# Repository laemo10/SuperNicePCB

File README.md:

# UWB Anchor & Indoor Human Occupancy Tracking Station

An integrated, multi-sensor UWB anchor PCB designed for real-time indoor object tracking (via Double-Sided Two-Way Ranging) and non-invasive human presence/occupancy monitoring. Built on a compact **75 × 85 mm²** 4-layer stackup, this node timestamps sensor data with microsecond precision via Wi-Fi TSF and streams payload telemetry to a central data fusion server.

## Table of Contents

* [Project Overview](#project-overview)
* [Key Features](#key-features)
* [Hardware & Bill of Materials](#hardware--bill-of-materials)
* [Sensor Matrix](#sensor-matrix)
* [Time Synchronization Strategy](#time-synchronization-strategy)
* [PCB Design & Stackup](#pcb-design--stackup)
* [Repository Structure](#repository-structure)
* [Team & Course Credits](#team--course-credits)

## Project Overview

This project implements an open-hardware anchor node for spatial localization and environmental occupancy analytics. The node performs two core functions simultaneously:

1. **Ultra-Wideband (UWB) Ranging:** Acts as a fixed anchor measuring distances to mobile UWB tags using IEEE 802.15.4z DS-TWR.
2. **Multi-Variable Human Sensing:** Tracks room occupancy trends and movement through non-camera environmental sensors (CO₂, Temperature/Humidity, Acoustic level, PIR motion, and mmWave micro-movement radar).

All gathered metrics are bound to a unified global timebase and transmitted over a 2.4 GHz Wi-Fi network (UDP/TCP) to a host server executing sensor-fusion algorithms.

## Key Features

* **High-Performance MCU:** ESP32-S3-WROOM-1-N8 (Dual-core Xtensa LX7 @ 240 MHz, 512 kB SRAM, 8 MB Flash, native USB CDC/JTAG).
* **Precision UWB Transceiver:** Decawave DWM3000TR13 (DW3110 engine) over SPI, supporting channels 5 (6.5 GHz) and 9 (8.0 GHz) with integrated antenna and keep-out area.
* **Dual 3.3V Power Domain Architecture:** Dedicated high-efficiency DC-DC Buck converter power rail for MCU processing and wireless transmission current spikes, combined with an isolated low-noise LDO regulator power rail for the sensitive sensor matrix.
* **Privacy-Preserving Human Detection:** Multi-variable sensing without optical cameras.
* **Microsecond Timestamping:** Hardware Wi-Fi TSF timer (`esp_wifi_get_tsf_time()`) combined with periodic NTP/SNTP synchronization.

## Hardware & Bill of Materials

| Function | Component MPN | Description | Interface | JLC Code |
| :--- | :--- | :--- | :--- | :--- |
| **MCU** | `ESP32-S3-WROOM-1-N8` | Dual-core Wi-Fi/BLE SoC (8 MB Flash) | SPI, I²C, UART, I²S | C2913198 |
| **UWB Transceiver** | `DWM3000TR13` | Integrated UWB Transceiver Module | SPI (20 MHz) | C5299931 |
| **MCU Power Rail** | `DC-DC Buck Regulator` | High-efficiency 3.3V Step-Down Converter (MCU) | Power | TBD |
| **Sensor Power Rail** | `Low-Noise LDO` | Dedicated Ultra-Low Noise 3.3V Regulator (Sensors) | Power | TBD |
| **Power Connector** | `HYCW263-USBC04-850B` | 16-Pin USB Type-C Receptacle | 5V Input | C3034197 |
| **CO₂ Sensor** | `Sensirion SCD40` | Photoacoustic NDIR CO₂ (0 - 40,000 ppm) | I²C | C3037696 |
| **Temp/RH** | `Sensirion SHT40-AD1B-R3` | Relative Humidity & Temperature Sensor | I²C | C2848306 |
| **Acoustic Sensor** | `TDK InvenSense ICS-43434` | Digital Omnidirectional MEMS Microphone | I²S | C5656610 |
| **PIR Motion** | `AM312` | Passive Infrared Human Motion Detector | GPIO | C114881 |
| **mmWave Radar** | `24/60 GHz mmWave Radar` | Micro-movement & Breathing Radar | UART | C37897213 |

## Sensor Matrix

1. **Decawave DWM3000 UWB:** Configured for Double-Sided Two-Way Ranging (DS-TWR) operating at 5 - 20 Hz update rates per tag.
2. **Sensirion SCD40:** Measures ambient CO₂ concentration every 30 - 60 s as an indicator of human breathing density.
3. **Sensirion SHT40:** Provides high-accuracy ambient thermal/humidity telemetry (±0.2 °C, ±1.8% RH) to complement indoor air comfort models.
4. **TDK ICS-43434:** Samples acoustic sound pressure over sliding time windows to determine room activity levels.
5. **AM312 PIR:** Digital motion trigger generating interrupts upon macroscopic body movement.
6. **mmWave Radar Module:** Captures fine target presence, velocity, and chest micro-movements (respiration) via continuous UART streaming.

## Time Synchronization Strategy

To ensure precise multi-anchor data alignment on the host processing server:

1. **Coarse Clock Sync (NTP/SNTP):** Upon Wi-Fi connection, the anchor queries an NTP server to calibrate epoch time.
2. **Fine-Grain Microsecond Timing (Wi-Fi TSF):** Each sensor frame is tagged using `esp_wifi_get_tsf_time()`, providing absolute microsecond precision relative to the Wi-Fi Access Point Timing Synchronization Function.
3. **Fallback Mode (ESP-NOW):** In ad-hoc deployments without an infrastructure AP, an ESP-NOW broadcast timesync protocol is utilized.

## PCB Design & Stackup

* **Dimensions:** 75 × 85 mm²
* **Layer Count:** 4 Layers (Mixed RF + High-Speed Digital)
* **Layer Assignment:**
  * **L1 (Top):** Component placement, high-speed signals (SPI, I²S, USB 90 Ω diff pair), RF traces.
  * **L2 (GND):** Continuous Solid Ground Plane.
  * **L3 (Power):** Split power planes with dual 3.3V power domains (3.3V_MCU from Buck, 3.3V_SENSOR from LDO).
  * **L4 (Bottom):** Secondary routing and test points.
* **RF Guidelines:** 50 Ω coplanar waveguide routing for UWB antenna path with explicit ground keep-out regions under the chip antenna area.

## Repository Structure

```
├── docs/
│   ├── schematics/             # PDF Schematics
│   └── specifications/         # ECAM Project Brief & Specs
├── hardware/
│   ├── gerber/                 # Production fabrication files
│   ├── KiCad/                  # Project files (.kicad_pro, .kicad_sch, .kicad_pcb)
│   └── bom/                    # Bill of Materials (CSV/JLCPCB format)
├── firmware/
│   ├── main/                   # ESP-IDF / Arduino source code
│   └── components/             # Custom drivers for SCD40, DWM3000, ICS-43434
└── README.md
```

## Team & Course Credits

**Course:** Advanced PCB Design (Academic Year 2026–2027)  
**Institution:** ECAM Brussels Engineering School  

**Group Members:**
* Laurent Emond
* Vincenzo Acquaviva
* Lincoln Lassey
* Mathieu Mascot

*ECAM Engineering Department*

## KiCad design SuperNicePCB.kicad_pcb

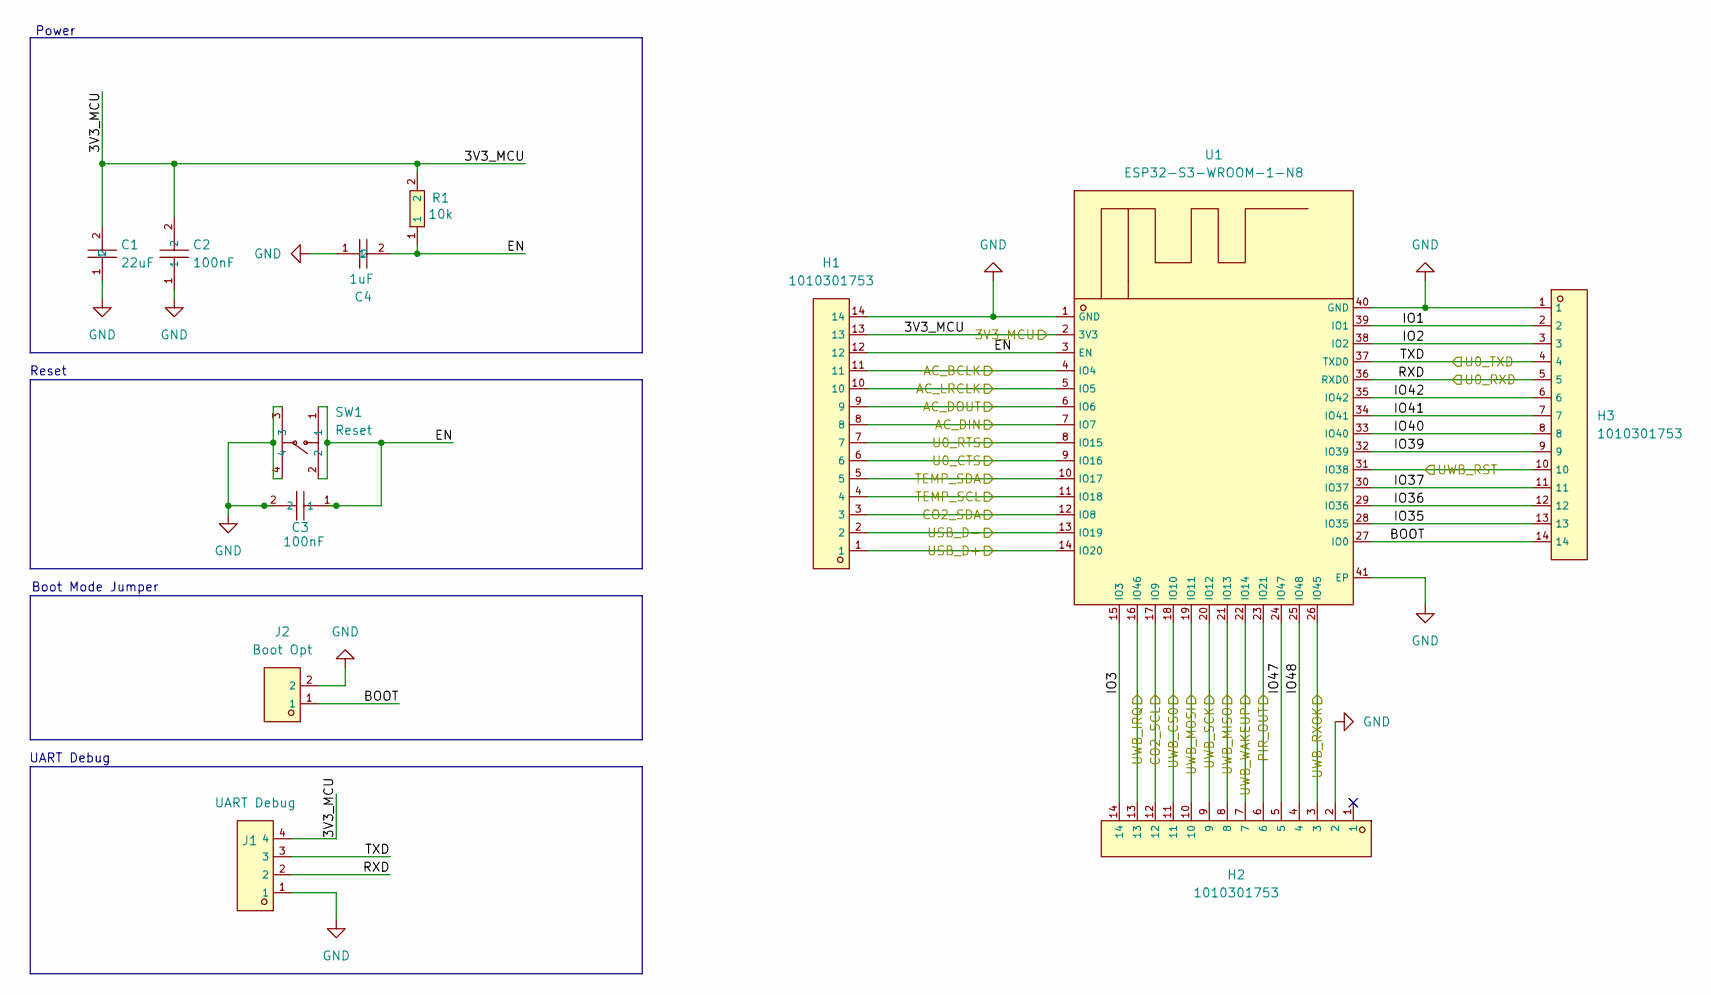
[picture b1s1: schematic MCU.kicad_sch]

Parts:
C1: 22uF; C1859_C1206; LCSC C1859
C2, C3: 100nF; C1525_C0402; LCSC C1525
C4: 1uF; C1592_C0603; LCSC C1592
H1, H2, H3: 1010301753; C52016809_HDR-SMD_14P-P2_54-V-M-S4_8; LCSC C52016809
J1: UART Debug; PinHeader_1x04_P1.27mm_Vertical_SMD_Pin1Left; LCSC C22438101
J2: Boot Opt; PinHeader_1x02_P1.27mm_Vertical_SMD_Pin1Left; LCSC C703015
R1: 10k; C1489_R1206; LCSC C1489
SW1: Reset; C55200589_SW-SMD_4P-L4_2-W3_4-P2_15-LS5_2; LCSC C55200589
U1: ESP32-S3-WROOM-1-N8; C2913198_WIFIM-SMD_ESP32-S3-WROOM-1-N8; LCSC C2913198

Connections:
/HumanSesors/AC_BCLK: H1.11, U1.4 (IO4); also elsewhere on the board
/HumanSesors/AC_LRCLK: H1.10, U1.5 (IO5); also elsewhere on the board
/HumanSesors/C02_SDA: H1.3, U1.12 (IO8); also elsewhere on the board
/HumanSesors/CO2_SCL: H2.12, U1.17 (IO9); also elsewhere on the board
/HumanSesors/DIN: H1.8, U1.7 (IO7); also elsewhere on the board
/HumanSesors/U0_CTS: H1.6, U1.9 (IO16); also elsewhere on the board
/HumanSesors/U0_RTS: H1.7, U1.8 (IO15); also elsewhere on the board
/MCU/3V3_MCU: C1.2, C2.2, H1.13, J1.4, R1.2, U1.2 (3V3); also elsewhere on the board
/MCU/AC_DOUT: H1.9, U1.6 (IO6)
/MCU/BOOT: H3.14, J2.1, U1.27 (IO0); also elsewhere on the board
/MCU/EN: C3.1, C4.2, H1.12, R1.1, SW1.1, SW1.2, U1.3 (EN)
/MCU/IO1: H3.2, U1.39 (IO1)
/MCU/IO2: H3.3, U1.38 (IO2)
/MCU/IO3: H2.14, U1.15 (IO3)
/MCU/IO35: H3.13, U1.28 (IO35)
/MCU/IO36: H3.12, U1.29 (IO36)
/MCU/IO37: H3.11, U1.30 (IO37)
/MCU/IO39: H3.9, U1.32 (IO39)
/MCU/IO40: H3.8, U1.33 (IO40)
/MCU/IO41: H3.7, U1.34 (IO41)
/MCU/IO42: H3.6, U1.35 (IO42)
/MCU/IO47: H2.5, U1.24 (IO47)
/MCU/IO48: H2.4, U1.25 (IO48)
/MCU/RXD: H3.5, J1.2, U1.36 (RXD0); also elsewhere on the board
/MCU/TXD: H3.4, J1.3, U1.37 (TXD0); also elsewhere on the board
/MCU/UWB_CS0: H2.11, U1.18 (IO10); also elsewhere on the board
/MCU/UWB_IRQ: H2.13, U1.16 (IO46); also elsewhere on the board
/MCU/UWB_MISO: H2.8, U1.21 (IO13); also elsewhere on the board
/MCU/UWB_MOSI: H2.10, U1.19 (IO11); also elsewhere on the board
/MCU/UWB_RST: H3.10, U1.31 (IO38); also elsewhere on the board
/MCU/UWB_RXOK: H2.3, U1.26 (IO45); also elsewhere on the board
/MCU/UWB_SCK: H2.9, U1.20 (IO12); also elsewhere on the board
/MCU/UWB_WAKEUP: H2.7, U1.22 (IO14); also elsewhere on the board
/PIR_OUT: H2.6, U1.23 (IO21); also elsewhere on the board
/TEMP_SCL: H1.4, U1.11 (IO18); also elsewhere on the board
/TEMP_SDA: H1.5, U1.10 (IO17); also elsewhere on the board
/USB_D+: H1.1, U1.14 (IO20); also elsewhere on the board
/USB_D-: H1.2, U1.13 (IO19); also elsewhere on the board
GND: C1.1, C2.1, C3.2, C4.1, H1.14, H2.2, H3.1, J1.1, J2.2, SW1.3, SW1.4, U1.1 (GND), U1.40 (GND), U1.41 (EP); also elsewhere on the board

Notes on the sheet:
Boot Mode Jumper
Power
UART Debug
Reset

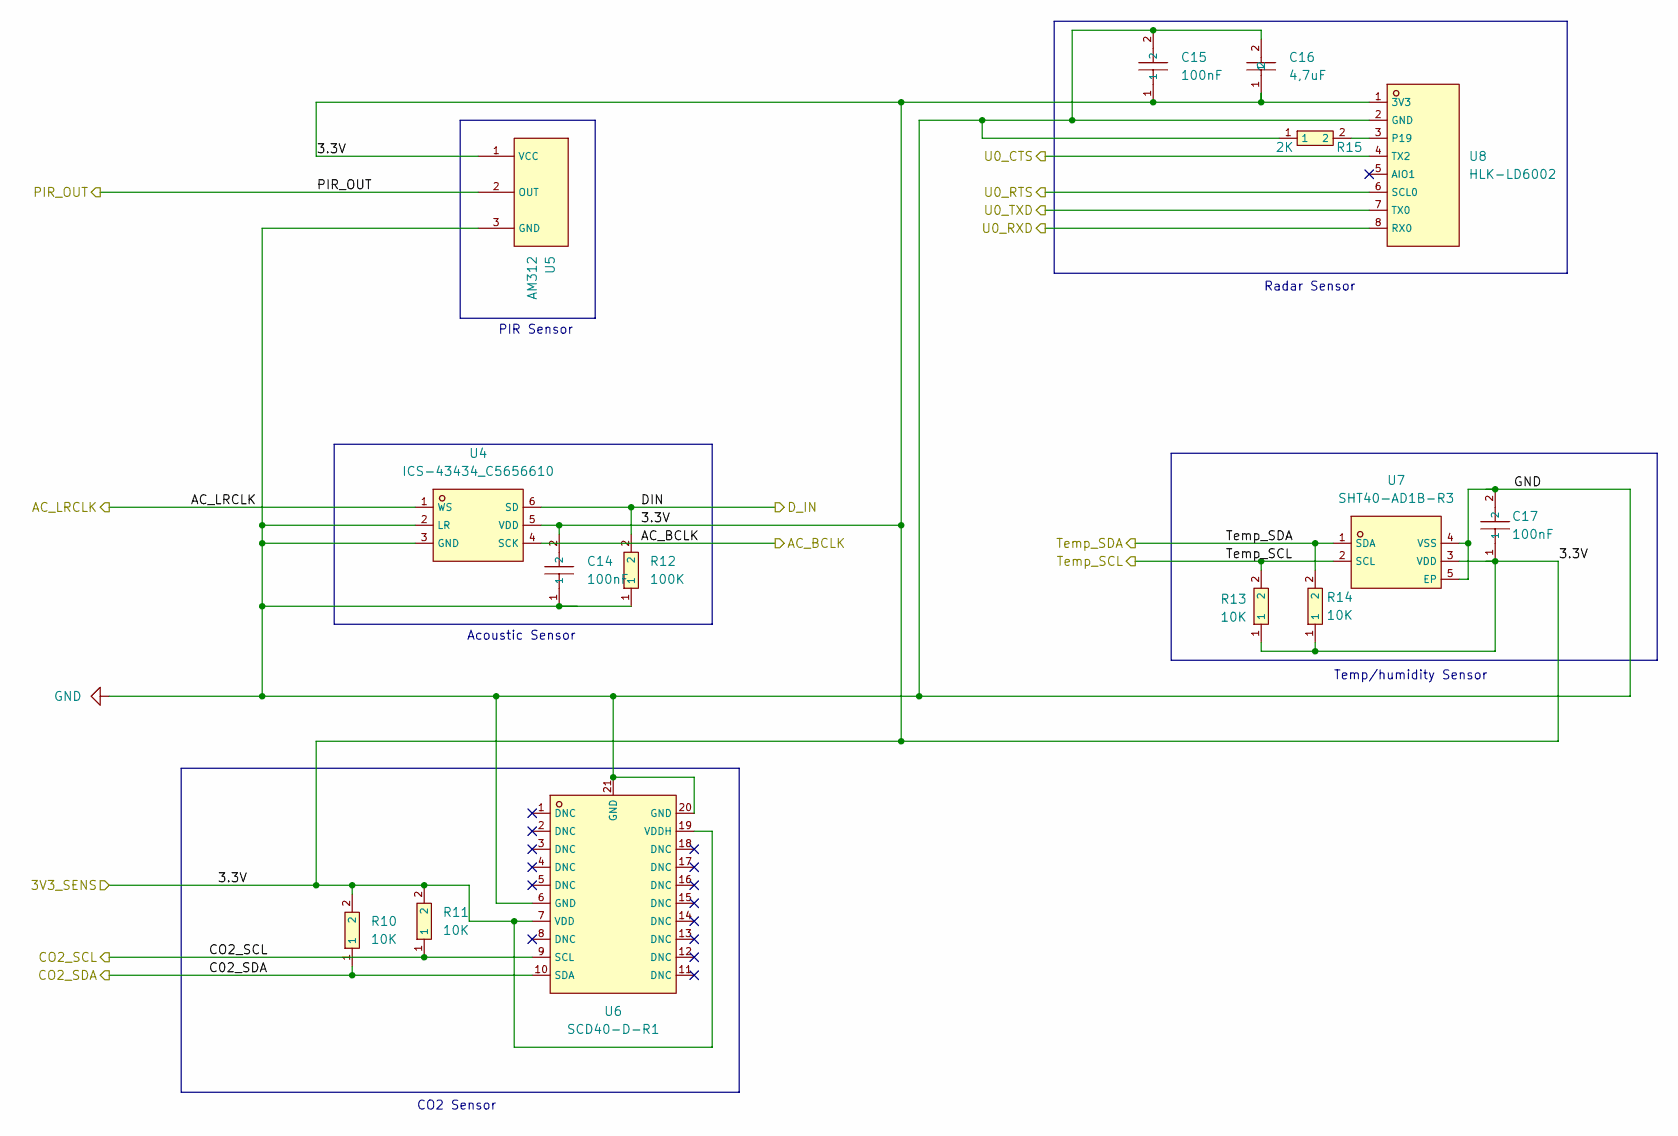
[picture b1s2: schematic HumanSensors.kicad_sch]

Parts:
C14, C15, C17: 100nF; C1525_C0402; LCSC C1525
C16: 4,7uF; C1705_C0603; LCSC C1705
R10, R11, R13, R14: 10K; C1489_R1206; LCSC C1489
R12: 100K; C14675_R0603; LCSC C14675
R15: 2K; C4109_R0402; LCSC C4109
U4: ICS-43434_C5656610; C5656610_MIC-SMD_6P-L3_5-W2_7-P0_90-BL; LCSC C5656610
U5: AM312; C114881_TO-5-3_L8_2-W8_2; LCSC C114881
U6: SCD40-D-R1; C3037696_LGA-20_L10_1-W10_1-P1_25-TL; LCSC C3037696
U7: SHT40-AD1B-R3; C2848306_DFN-4_L1_5-W1_5-P0_8-TL-EP; LCSC C2848306
U8: HLK-LD6002; C37897213_SENSOR-TH_HLK-LD6002; LCSC C37897213

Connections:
/HumanSesors/3.3V: C14.2, C15.1, C16.1, C17.1, R10.2, R11.2, R13.1, R14.1, U4.5 (VDD), U5.1 (VCC), U6.7 (VDD), U6.19 (VDDH), U7.3 (VDD), U8.1 (3V3); also elsewhere on the board
/HumanSesors/AC_BCLK: U4.4 (SCK); also elsewhere on the board
/HumanSesors/AC_LRCLK: U4.1 (WS); also elsewhere on the board
/HumanSesors/C02_SDA: R10.1, U6.10 (SDA); also elsewhere on the board
/HumanSesors/CO2_SCL: R11.1, U6.9 (SCL); also elsewhere on the board
/HumanSesors/DIN: R12.2, U4.6 (SD); also elsewhere on the board
/HumanSesors/U0_CTS: U8.4 (TX2); also elsewhere on the board
/HumanSesors/U0_RTS: U8.6 (SCL0); also elsewhere on the board
/MCU/RXD: U8.8 (RX0); also elsewhere on the board
/MCU/TXD: U8.7 (TX0); also elsewhere on the board
/PIR_OUT: U5.2 (OUT); also elsewhere on the board
/TEMP_SCL: R13.2, U7.2 (SCL); also elsewhere on the board
/TEMP_SDA: R14.2, U7.1 (SDA); also elsewhere on the board
GND: C14.1, C15.2, C16.2, C17.2, R12.1, R15.1, U4.2 (LR), U4.3 (GND), U5.3 (GND), U6.6 (GND), U6.20 (GND), U6.21 (GND), U7.4 (VSS), U7.5 (EP), U8.2 (GND); also elsewhere on the board
unnamed: R15.2, U8.3 (P19)

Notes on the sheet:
Acoustic Sensor
PIR Sensor
Radar Sensor
Temp/humidity Sensor
CO2 Sensor

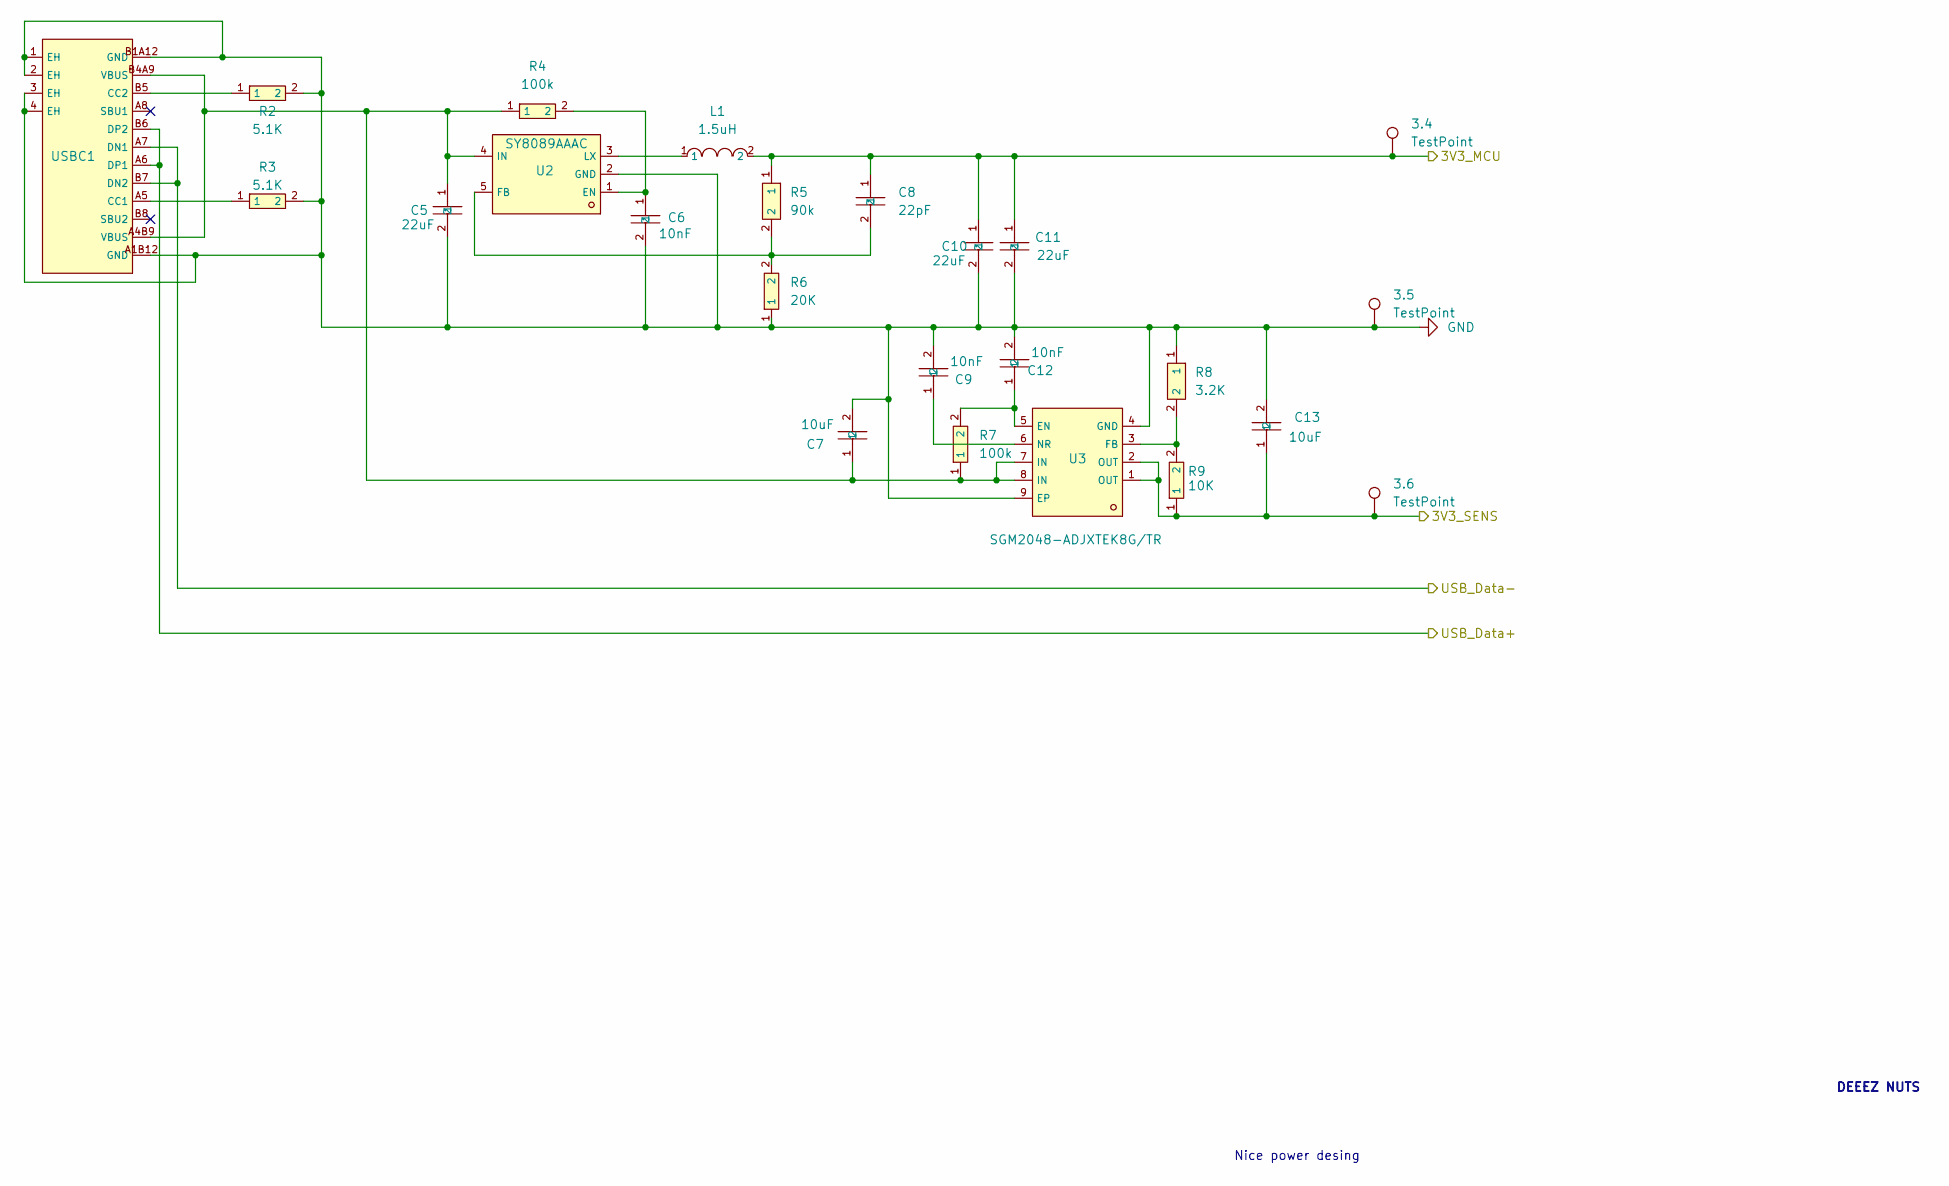
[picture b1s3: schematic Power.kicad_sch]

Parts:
3.4, 3.5, 3.6: TestPoint; TestPoint_Pad_1.0x1.0mm
C5, C10, C11: 22uF; C109448_C0603; LCSC C109448
C6, C9, C12: 10nF; C1589_C0603; LCSC C1589
C7, C13: 10uF; C1713_C0805; LCSC C1713
C8: 22pF; C76919_C0201; LCSC C76919
L1: 1.5uH; C42100_IND-SMD_L4_0-W4_0; LCSC C42100
R2, R3: 5.1K; C14677_R0603; LCSC C14677
R4, R7: 100k; C14675_R0603; LCSC C14675
R5: 90k; C871504_R1206; LCSC C871504
R6: 20K; C4184_R0603; LCSC C4184
R8: 3.2K; C705066_R0402; LCSC C705066
R9: 10K; C1489_R1206; LCSC C1489
U2: SY8089AAAC; C78988_SOT-23-5_L3_0-W1_7-P0_95-LS2_8-BR; LCSC C78988
U3: SGM2048-ADJXTEK8G/TR; C3294704_VDFN-8_L3_0-W3_0-P0_65-BL-EP; LCSC C3294704
USBC1: TYPE-C-31-M-12; C165948_USB-C_SMD-TYPE-C-31-M-12_1; LCSC C165948

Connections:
/HumanSesors/3.3V: C13.1, R9.1, U3.1 (OUT), U3.2 (OUT); also elsewhere on the board
/MCU/3V3_MCU: C8.1, C10.1, C11.1, L1.2, R5.1; also elsewhere on the board
/USB_D+: USBC1.A6 (DP1), USBC1.B6 (DP2); also elsewhere on the board
/USB_D-: USBC1.A7 (DN1), USBC1.B7 (DN2); also elsewhere on the board
GND: C5.2, C6.2, C7.2, C9.2, C10.2, C11.2, C12.2, C13.2, R2.2, R3.2, R6.1, R8.1, U2.2 (GND), U3.4 (GND), U3.9 (EP), USBC1.1 (EH), USBC1.2 (EH), USBC1.3 (EH), USBC1.4 (EH), USBC1.A1B12 (GND), USBC1.B1A12 (GND); also elsewhere on the board
unnamed: C6.1, R4.2, U2.1 (EN)
unnamed: C8.2, R5.2, R6.2, U2.5 (FB)
unnamed: C5.1, C7.1, R4.1, R7.1, U2.4 (IN), U3.7 (IN), U3.8 (IN), USBC1.A4B9 (VBUS), USBC1.B4A9 (VBUS)
unnamed: L1.1, U2.3 (LX)
unnamed: C12.1, R7.2, U3.5 (EN)
unnamed: R8.2, R9.2, U3.3 (FB)
unnamed: C9.1, U3.6 (NR)
unnamed: R3.1, USBC1.A5 (CC1)
unnamed: R2.1, USBC1.B5 (CC2)

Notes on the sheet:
Nice power desing
DEEEZ NUTS

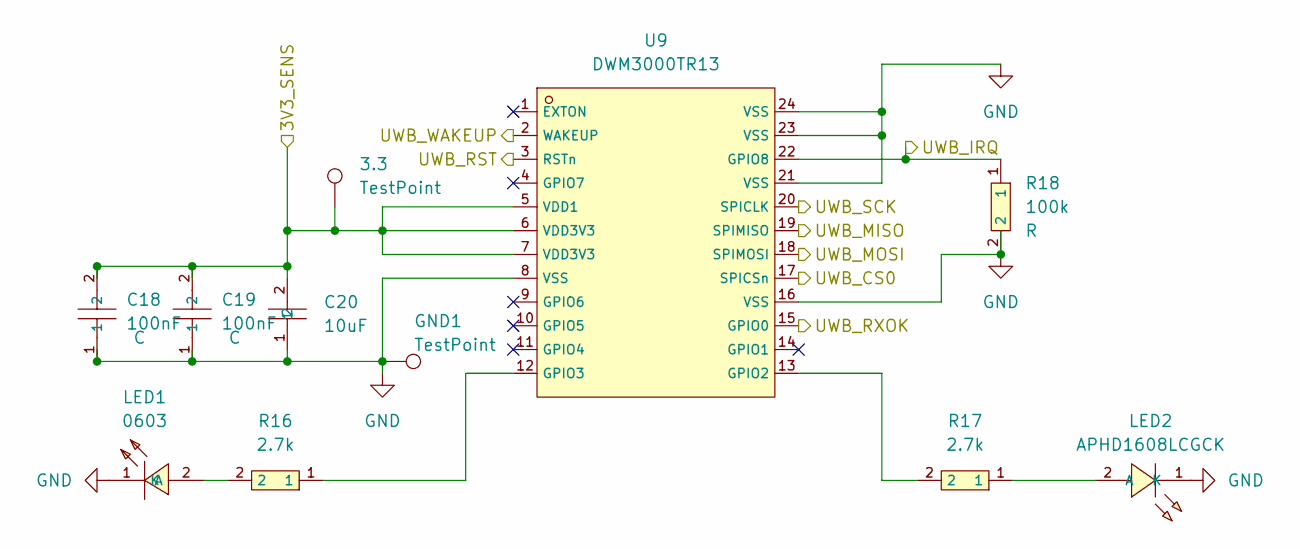
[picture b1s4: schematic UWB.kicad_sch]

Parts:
3.3: TestPoint; TestPoint_Pad_1.0x1.0mm
C18, C19: 100nF; C1525_C0402; LCSC C1525
C20: 10uF; C1713_C0805; LCSC C1713
GND1: TestPoint; TestPoint_Pad_1.0x1.0mm
LED1: 0603; C2289_LED0603-RD; LCSC C2289
LED2: APHD1608LCGCK; C5139863_LED-SMD_L1_6-W0_8-RD_GREEN-1; LCSC C5139863
R16, R17: 2.7k; C13167_R0603; LCSC C13167
R18: 100k; C14675_R0603; LCSC C14675
U9: DWM3000TR13; C5299931_WIRELM-SMD_DWM3000TR13; LCSC C5299931

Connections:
/HumanSesors/3.3V: 3.3.1 (1_1), C18.2, C19.2, C20.2, U9.5 (VDD1), U9.6 (VDD3V3), U9.7 (VDD3V3); also elsewhere on the board
/MCU/UWB_CS0: U9.17 (SPICSn); also elsewhere on the board
/MCU/UWB_IRQ: R18.1, U9.22 (GPIO8); also elsewhere on the board
/MCU/UWB_MISO: U9.19 (SPIMISO); also elsewhere on the board
/MCU/UWB_MOSI: U9.18 (SPIMOSI); also elsewhere on the board
/MCU/UWB_RST: U9.3 (RSTn); also elsewhere on the board
/MCU/UWB_RXOK: U9.15 (GPIO0); also elsewhere on the board
/MCU/UWB_SCK: U9.20 (SPICLK); also elsewhere on the board
/MCU/UWB_WAKEUP: U9.2 (WAKEUP); also elsewhere on the board
GND: C18.1, C19.1, C20.1, GND1.1, LED1.1 (K), LED2.1 (K), R18.2, U9.8 (VSS), U9.16 (VSS), U9.21 (VSS), U9.23 (VSS), U9.24 (VSS); also elsewhere on the board
unnamed: LED1.2 (A), R16.2
unnamed: LED2.2 (A), R17.1
unnamed: R17.2, U9.13 (GPIO2)
unnamed: R16.1, U9.12 (GPIO3)

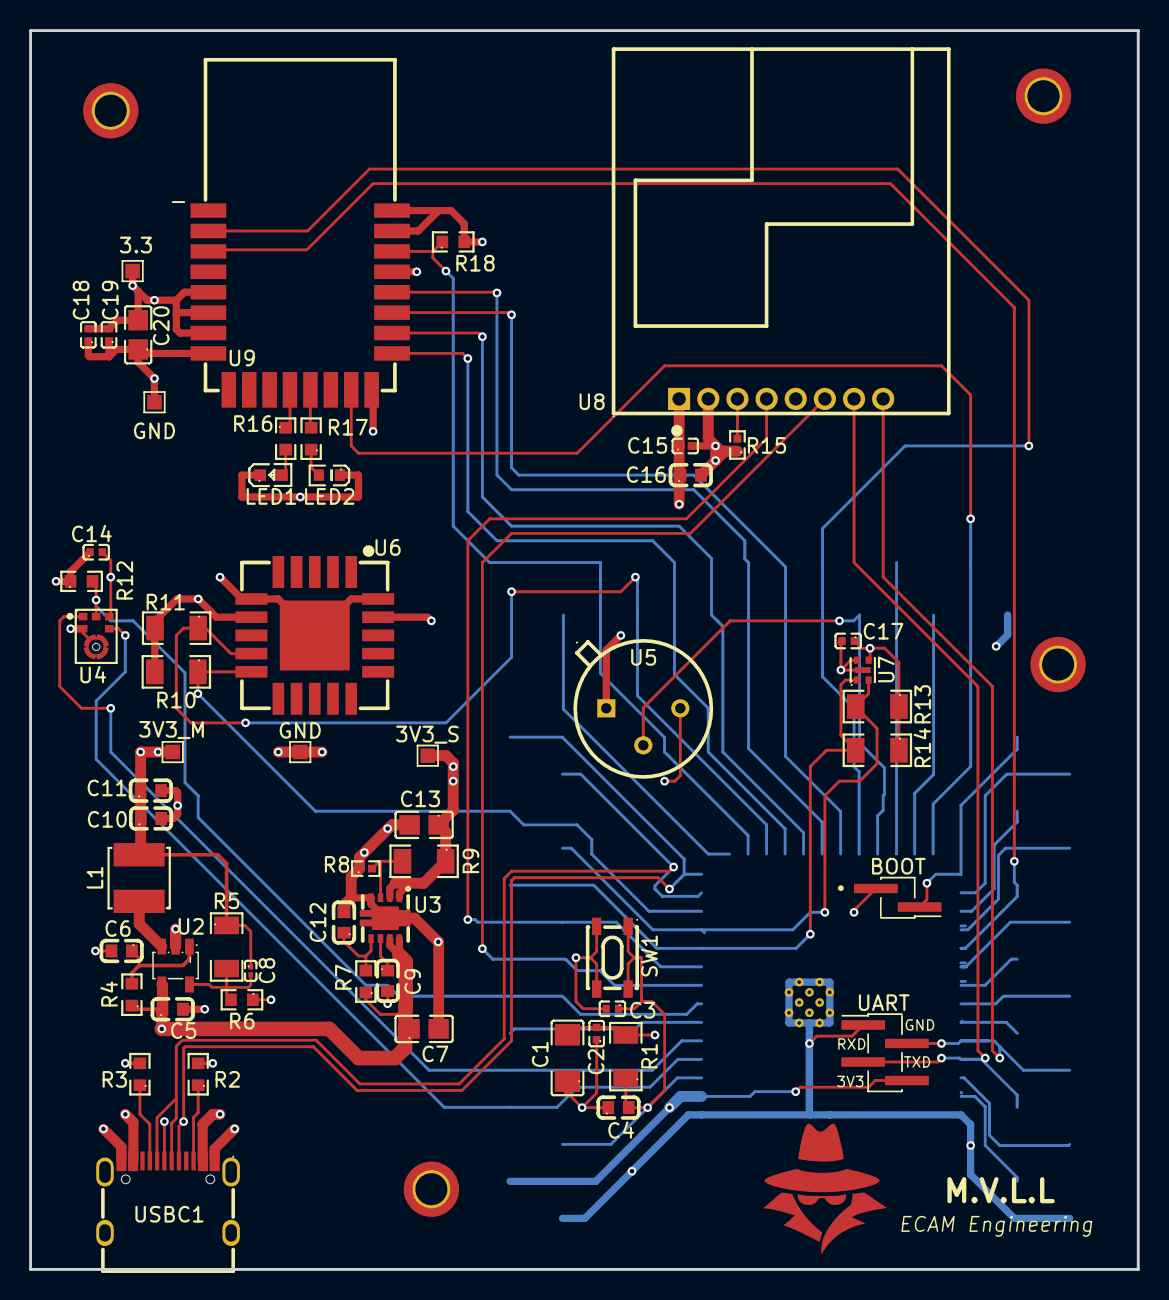
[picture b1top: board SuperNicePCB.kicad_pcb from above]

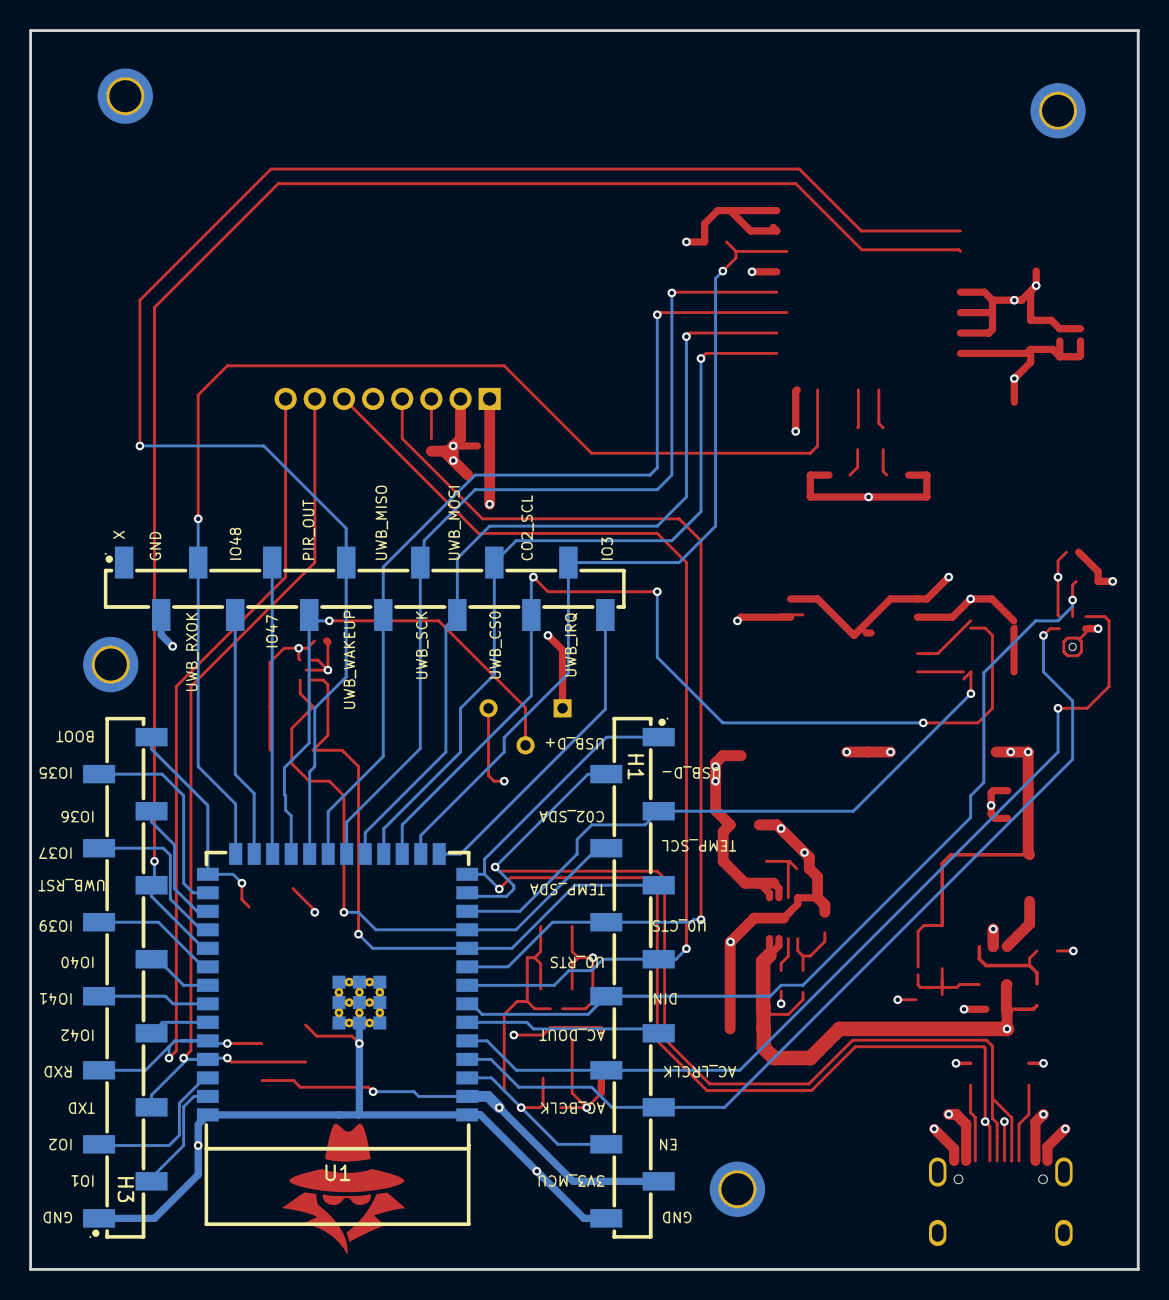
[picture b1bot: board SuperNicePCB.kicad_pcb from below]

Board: 4 copper layers, 76.0 x 85.0 mm, 62 parts (4 on the bottom side), 54 nets.

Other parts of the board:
3V3_M, 3V3_S: TestPoint; TestPoint_Pad_1.0x1.0mm
BOOT: Boot Opt; PinHeader_1x02_P1.27mm_Vertical_SMD_Pin1Left
GND: TestPoint; TestPoint_Pad_1.0x1.0mm
GND#2: TestPoint; TestPoint_Pad_1.0x1.0mm
UART: UART Debug; PinHeader_1x04_P1.27mm_Vertical_SMD_Pin1Left

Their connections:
/HumanSesors/3.3V: 3V3_S.1 (1_1); also elsewhere on the board
/MCU/3V3_MCU: 3V3_M.1 (1_1), UART.4; also elsewhere on the board
/MCU/BOOT: BOOT.1; also elsewhere on the board
/MCU/RXD: UART.2; also elsewhere on the board
/MCU/TXD: UART.3; also elsewhere on the board
GND: BOOT.2, GND.1 (1_1), GND#2.1 (1_1), UART.1; also elsewhere on the board
